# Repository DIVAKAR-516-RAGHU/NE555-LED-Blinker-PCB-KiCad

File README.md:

# NE555 LED Blinker PCB Design

## Project Overview

This project demonstrates the schematic design and PCB layout of an LED blinker circuit based on the NE555 timer IC, configured as an astable multivibrator.

## Tools Used

* KiCad 10.0
* KiCad Schematic Editor
* KiCad PCB Editor
* KiCad Gerber Viewer

## Project Features

* NE555 astable multivibrator circuit
* Through-hole component layout
* PCB track routing
* PCB board outline using the Edge.Cuts layer
* Gerber fabrication file generation
* Drill file generation

## Project Structure

* `Schematic/` — Circuit schematic
* `PCB/` — KiCad PCB and project files
* `Gerber/` — Gerber layers and drill file
* `Images/` — Project screenshots

## Fabrication Outputs

The `Gerber/` directory contains copper, solder mask, silkscreen and board-outline files, along with the drill file required for PCB fabrication.

## Learning Outcomes

* Understanding the NE555 astable multivibrator
* Schematic capture and PCB layout using KiCad
* Through-hole component placement and track routing
* Preparing Gerber and drill outputs

## Project Status

PCB layout and fabrication-file generation completed. Physical PCB fabrication and testing are not yet confirmed.

## Author

Divakar R
B.E. Electronics and Communication Engineering

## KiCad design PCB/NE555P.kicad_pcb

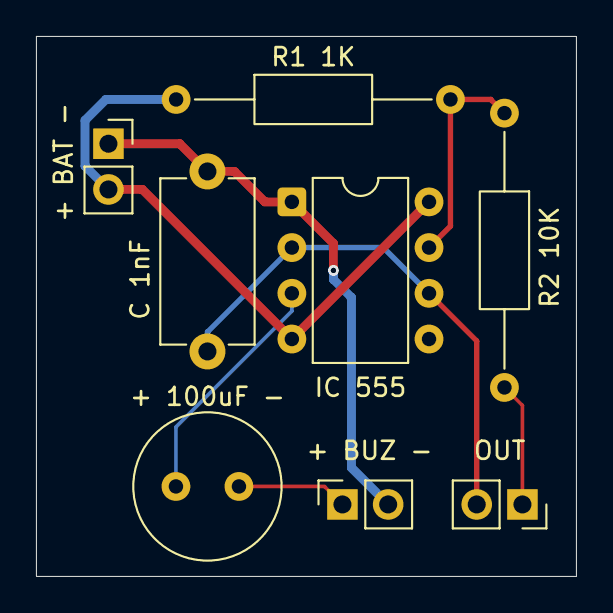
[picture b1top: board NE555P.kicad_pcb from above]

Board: 2 copper layers, 30.0 x 30.0 mm, 8 parts (0 on the bottom side), 7 nets.

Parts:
+ 100uF -: C_Polarized; C_Radial_D8.0mm_H11.5mm_P3.50mm
+ BAT -: Battery; PinSocket_1x02_P2.54mm_Vertical
+ BUZ -: Buzzer; PinSocket_1x02_P2.54mm_Vertical
C 1nF: 1nF; C_Disc_D9.0mm_W5.0mm_P10.00mm
IC 555: NE555P; DIP-8_W7.62mm
OUT: HOOMANS; PinSocket_1x02_P2.54mm_Vertical
R1 1K: 1K; R_Axial_DIN0207_L6.3mm_D2.5mm_P15.24mm_Horizontal
R2 10K: 10K; R_Axial_DIN0207_L6.3mm_D2.5mm_P15.24mm_Horizontal

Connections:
/DIS: IC 555.7 (DISCH), R1 1K.2, R2 10K.1
/Out: + 100uF -.1, IC 555.3 (OUT)
/TR: C 1nF.1, IC 555.2 (TRIG), IC 555.6 (THRES), OUT.2
GND: + BAT -.1, + BUZ -.2, C 1nF.2, IC 555.1 (GND)
unnamed: + 100uF -.2, + BUZ -.1
unnamed: OUT.1, R2 10K.2
VCC: + BAT -.2, IC 555.4 (~RST), IC 555.8 (VCC), R1 1K.1
